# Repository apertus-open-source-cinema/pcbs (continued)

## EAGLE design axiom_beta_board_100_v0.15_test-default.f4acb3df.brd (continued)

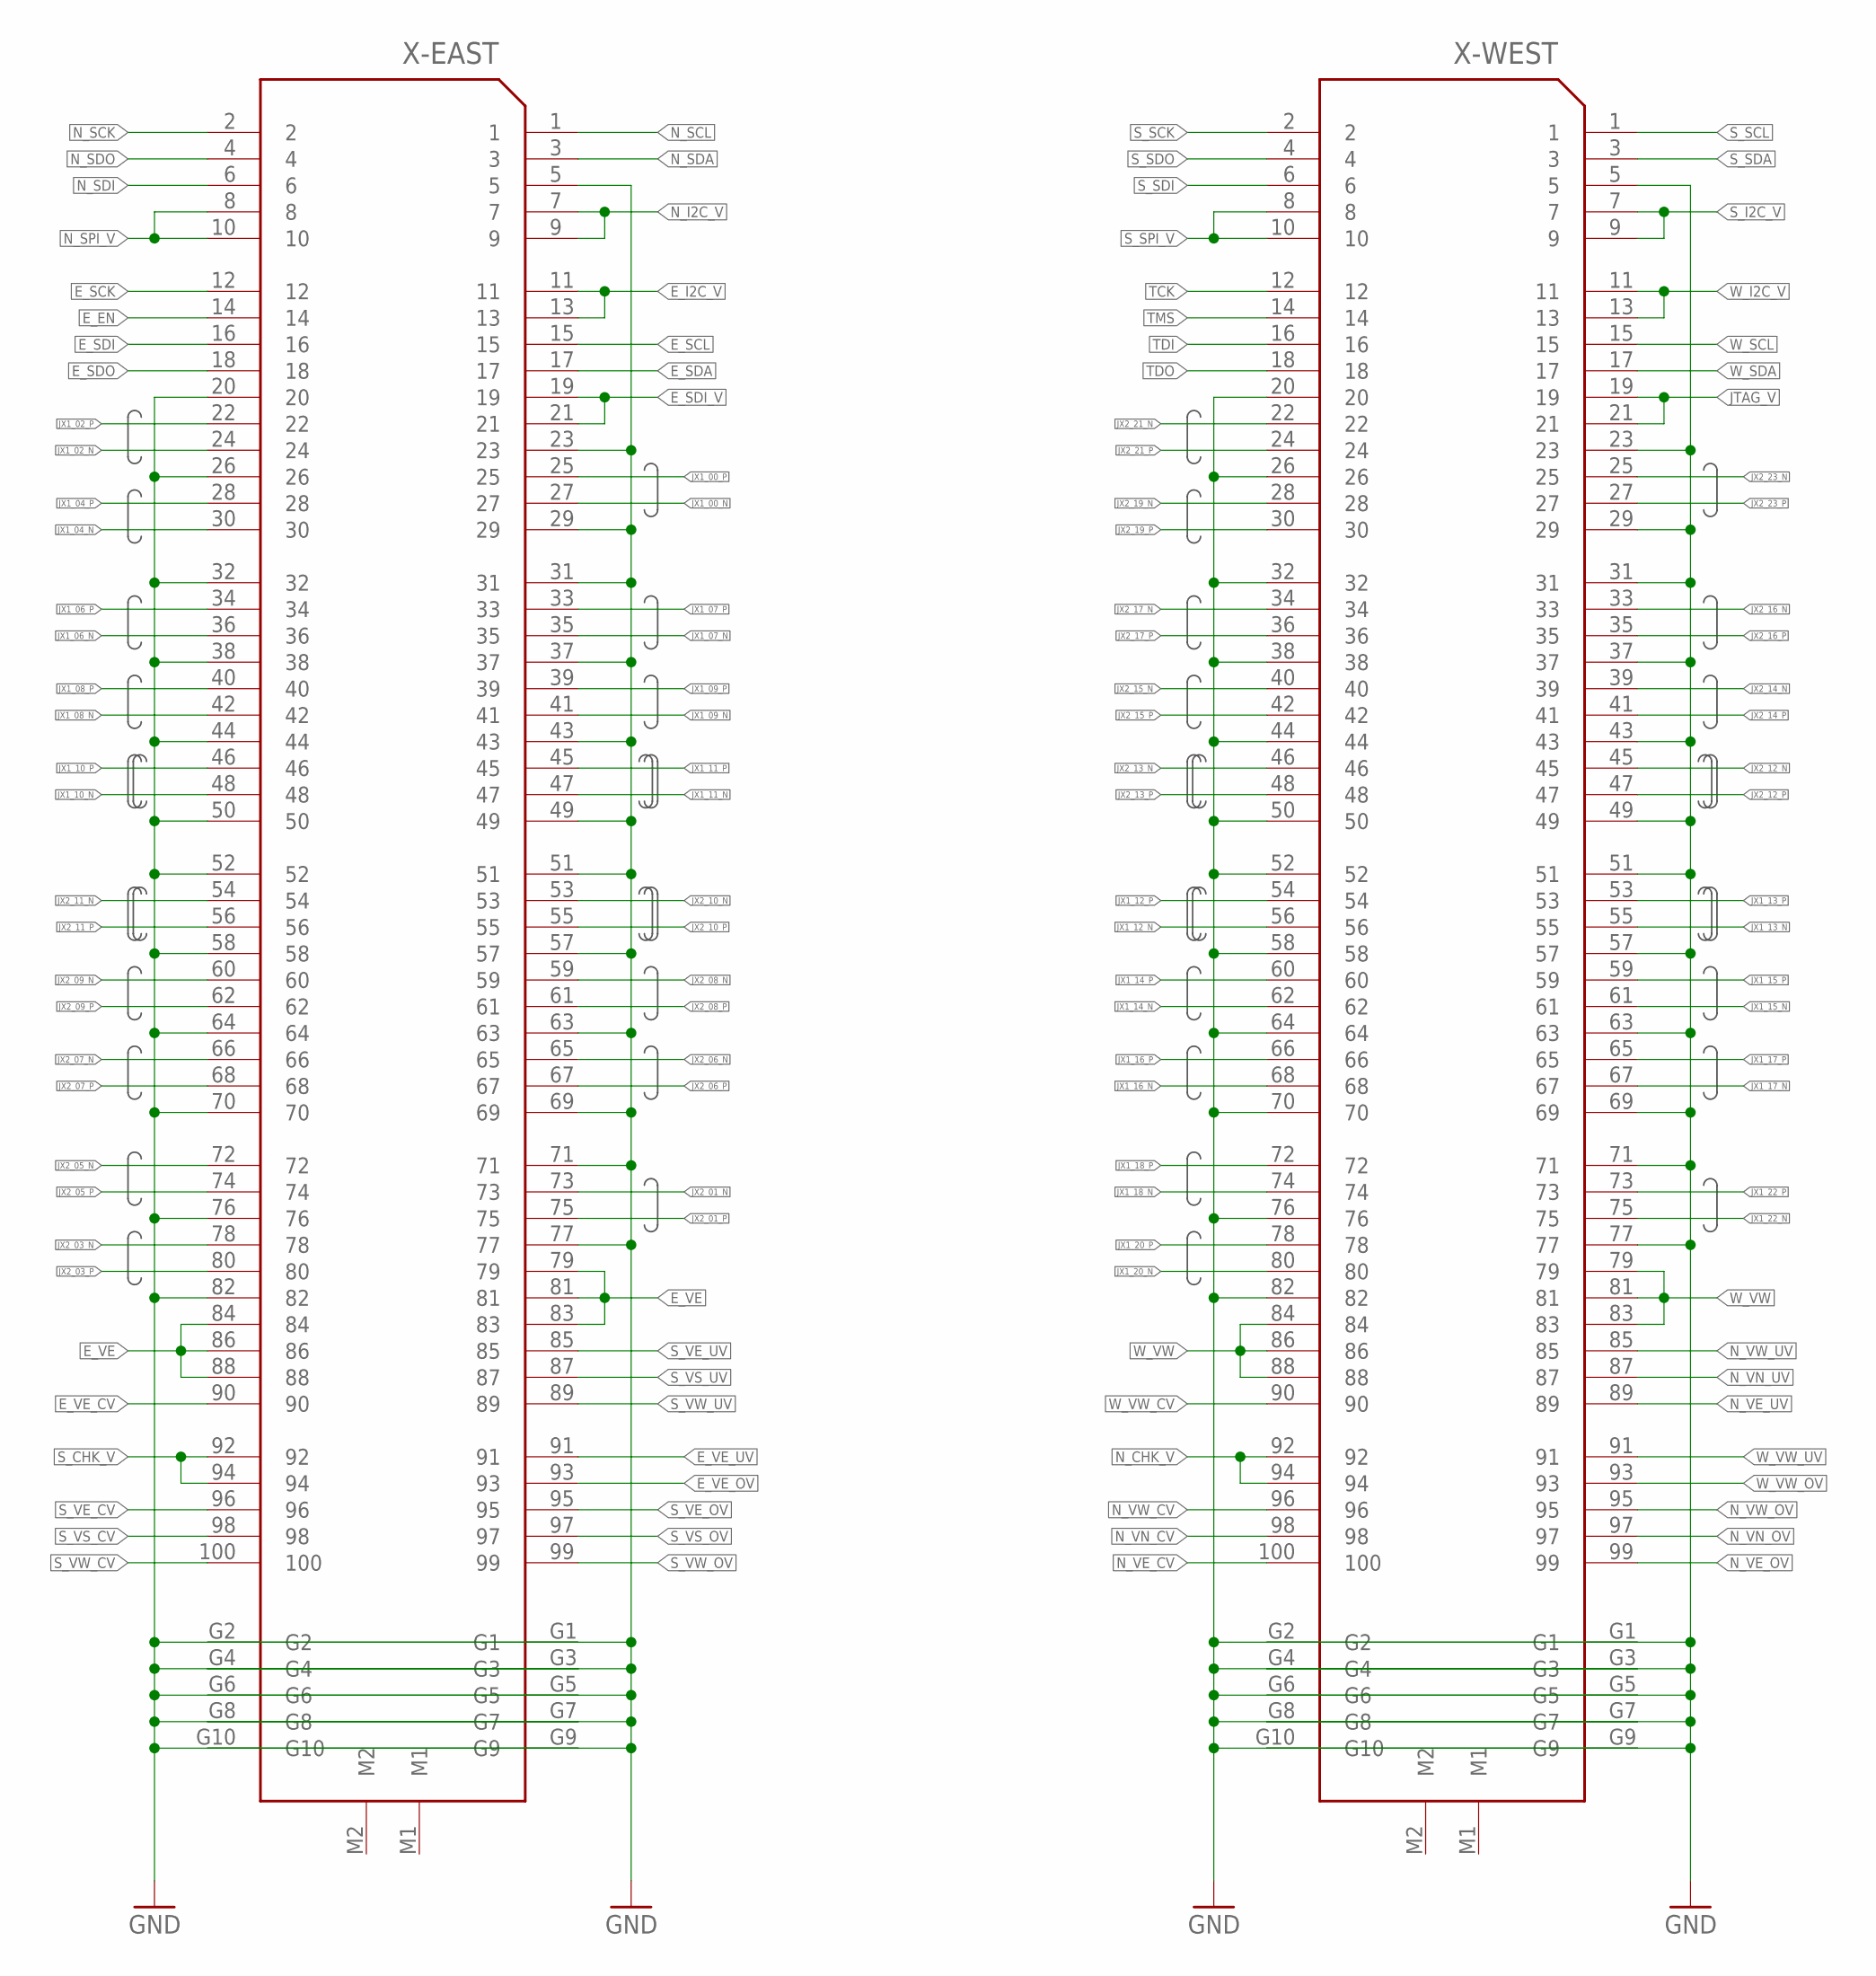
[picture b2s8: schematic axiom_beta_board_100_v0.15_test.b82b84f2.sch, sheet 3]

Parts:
X-EAST: FX10-100/10S; FX10A-100S/10
X-WEST: FX10-100/10S; FX10A-100S/10

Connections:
E_EN: X-EAST.14; also elsewhere on the board
E_I2C_V: X-EAST.11, X-EAST.13; also elsewhere on the board
E_SCK: X-EAST.12; also elsewhere on the board
E_SCL: X-EAST.15; also elsewhere on the board
E_SDA: X-EAST.17; also elsewhere on the board
E_SDI: X-EAST.16; also elsewhere on the board
E_SDI_V: X-EAST.19, X-EAST.21; also elsewhere on the board
E_SDO: X-EAST.18; also elsewhere on the board
E_VE: X-EAST.79, X-EAST.81, X-EAST.83, X-EAST.84, X-EAST.86, X-EAST.88; also elsewhere on the board
E_VE_CV: X-EAST.90; also elsewhere on the board
E_VE_OV: X-EAST.93; also elsewhere on the board
E_VE_UV: X-EAST.91; also elsewhere on the board
GND: X-EAST.5, X-EAST.20, X-EAST.23, X-EAST.26, X-EAST.29, X-EAST.31, X-EAST.32, X-EAST.37, X-EAST.38, X-EAST.43, X-EAST.44, X-EAST.49, X-EAST.50, X-EAST.51, X-EAST.52, X-EAST.57, X-EAST.58, X-EAST.63, X-EAST.64, X-EAST.69, X-EAST.70, X-EAST.71, X-EAST.76, X-EAST.77, X-EAST.82, X-EAST.G1, X-EAST.G2, X-EAST.G3, X-EAST.G4, X-EAST.G5, X-EAST.G6, X-EAST.G7, X-EAST.G8, X-EAST.G9, X-EAST.G10, X-WEST.5, X-WEST.20, X-WEST.23, X-WEST.26, X-WEST.29, X-WEST.31, X-WEST.32, X-WEST.37, X-WEST.38, X-WEST.43, X-WEST.44, X-WEST.49, X-WEST.50, X-WEST.51, X-WEST.52, X-WEST.57, X-WEST.58, X-WEST.63, X-WEST.64, X-WEST.69, X-WEST.70, X-WEST.71, X-WEST.76, X-WEST.77, X-WEST.82, X-WEST.G1, X-WEST.G2, X-WEST.G3, X-WEST.G4, X-WEST.G5, X-WEST.G6, X-WEST.G7, X-WEST.G8, X-WEST.G9, X-WEST.G10; also elsewhere on the board
JTAG_V: X-WEST.19, X-WEST.21; also elsewhere on the board
JX1_00_N: X-EAST.27; also elsewhere on the board
JX1_00_P: X-EAST.25; also elsewhere on the board
JX1_02_N: X-EAST.24; also elsewhere on the board
JX1_02_P: X-EAST.22; also elsewhere on the board
JX1_04_N: X-EAST.30; also elsewhere on the board
JX1_04_P: X-EAST.28; also elsewhere on the board
JX1_06_N: X-EAST.36; also elsewhere on the board
JX1_06_P: X-EAST.34; also elsewhere on the board
JX1_07_N: X-EAST.35; also elsewhere on the board
JX1_07_P: X-EAST.33; also elsewhere on the board
JX1_08_N: X-EAST.42; also elsewhere on the board
JX1_08_P: X-EAST.40; also elsewhere on the board
JX1_09_N: X-EAST.41; also elsewhere on the board
JX1_09_P: X-EAST.39; also elsewhere on the board
JX1_10_N: X-EAST.48; also elsewhere on the board
JX1_10_P: X-EAST.46; also elsewhere on the board
JX1_11_N: X-EAST.47; also elsewhere on the board
JX1_11_P: X-EAST.45; also elsewhere on the board
JX1_12_N: X-WEST.56; also elsewhere on the board
JX1_12_P: X-WEST.54; also elsewhere on the board
JX1_13_N: X-WEST.55; also elsewhere on the board
JX1_13_P: X-WEST.53; also elsewhere on the board
JX1_14_N: X-WEST.62; also elsewhere on the board
JX1_14_P: X-WEST.60; also elsewhere on the board
JX1_15_N: X-WEST.61; also elsewhere on the board
JX1_15_P: X-WEST.59; also elsewhere on the board
JX1_16_N: X-WEST.68; also elsewhere on the board
JX1_16_P: X-WEST.66; also elsewhere on the board
JX1_17_N: X-WEST.67; also elsewhere on the board
JX1_17_P: X-WEST.65; also elsewhere on the board
JX1_18_N: X-WEST.74; also elsewhere on the board
JX1_18_P: X-WEST.72; also elsewhere on the board
JX1_20_N: X-WEST.80; also elsewhere on the board
JX1_20_P: X-WEST.78; also elsewhere on the board
JX1_22_N: X-WEST.75; also elsewhere on the board
JX1_22_P: X-WEST.73; also elsewhere on the board
JX2_01_N: X-EAST.73; also elsewhere on the board
JX2_01_P: X-EAST.75; also elsewhere on the board
JX2_03_N: X-EAST.78; also elsewhere on the board
JX2_03_P: X-EAST.80; also elsewhere on the board
JX2_05_N: X-EAST.72; also elsewhere on the board
JX2_05_P: X-EAST.74; also elsewhere on the board
JX2_06_N: X-EAST.65; also elsewhere on the board
JX2_06_P: X-EAST.67; also elsewhere on the board
JX2_07_N: X-EAST.66; also elsewhere on the board
JX2_07_P: X-EAST.68; also elsewhere on the board
JX2_08_N: X-EAST.59; also elsewhere on the board
JX2_08_P: X-EAST.61; also elsewhere on the board
JX2_09_N: X-EAST.60; also elsewhere on the board
JX2_09_P: X-EAST.62; also elsewhere on the board
JX2_10_N: X-EAST.53; also elsewhere on the board
JX2_10_P: X-EAST.55; also elsewhere on the board
JX2_11_N: X-EAST.54; also elsewhere on the board
JX2_11_P: X-EAST.56; also elsewhere on the board
JX2_12_N: X-WEST.45; also elsewhere on the board
JX2_12_P: X-WEST.47; also elsewhere on the board
JX2_13_N: X-WEST.46; also elsewhere on the board
JX2_13_P: X-WEST.48; also elsewhere on the board
JX2_14_N: X-WEST.39; also elsewhere on the board
JX2_14_P: X-WEST.41; also elsewhere on the board
JX2_15_N: X-WEST.40; also elsewhere on the board
JX2_15_P: X-WEST.42; also elsewhere on the board
JX2_16_N: X-WEST.33; also elsewhere on the board
JX2_16_P: X-WEST.35; also elsewhere on the board
JX2_17_N: X-WEST.34; also elsewhere on the board
JX2_17_P: X-WEST.36; also elsewhere on the board
JX2_19_N: X-WEST.28; also elsewhere on the board
JX2_19_P: X-WEST.30; also elsewhere on the board
JX2_21_N: X-WEST.22; also elsewhere on the board
JX2_21_P: X-WEST.24; also elsewhere on the board
JX2_23_N: X-WEST.25; also elsewhere on the board
JX2_23_P: X-WEST.27; also elsewhere on the board
N_CHK_V: X-WEST.92, X-WEST.94; also elsewhere on the board
N_I2C_V: X-EAST.7, X-EAST.9; also elsewhere on the board
N_SCK: X-EAST.2; also elsewhere on the board
N_SCL: X-EAST.1; also elsewhere on the board
N_SDA: X-EAST.3; also elsewhere on the board
N_SDI: X-EAST.6; also elsewhere on the board
N_SDO: X-EAST.4; also elsewhere on the board
N_SPI_V: X-EAST.8, X-EAST.10; also elsewhere on the board
N_VE_CV: X-WEST.100; also elsewhere on the board
N_VE_OV: X-WEST.99; also elsewhere on the board
N_VE_UV: X-WEST.89; also elsewhere on the board
N_VN_CV: X-WEST.98; also elsewhere on the board
N_VN_OV: X-WEST.97; also elsewhere on the board
N_VN_UV: X-WEST.87; also elsewhere on the board
N_VW_CV: X-WEST.96; also elsewhere on the board
N_VW_OV: X-WEST.95; also elsewhere on the board
N_VW_UV: X-WEST.85; also elsewhere on the board
S_CHK_V: X-EAST.92, X-EAST.94; also elsewhere on the board
S_I2C_V: X-WEST.7, X-WEST.9; also elsewhere on the board
S_SCK: X-WEST.2; also elsewhere on the board
S_SCL: X-WEST.1; also elsewhere on the board
S_SDA: X-WEST.3; also elsewhere on the board
S_SDI: X-WEST.6; also elsewhere on the board
S_SDO: X-WEST.4; also elsewhere on the board
S_SPI_V: X-WEST.8, X-WEST.10; also elsewhere on the board
S_VE_CV: X-EAST.96; also elsewhere on the board
S_VE_OV: X-EAST.95; also elsewhere on the board
S_VE_UV: X-EAST.85; also elsewhere on the board
S_VS_CV: X-EAST.98; also elsewhere on the board
S_VS_OV: X-EAST.97; also elsewhere on the board
S_VS_UV: X-EAST.87; also elsewhere on the board
S_VW_CV: X-EAST.100; also elsewhere on the board
S_VW_OV: X-EAST.99; also elsewhere on the board
S_VW_UV: X-EAST.89; also elsewhere on the board
TCK: X-WEST.12; also elsewhere on the board
TDI: X-WEST.16; also elsewhere on the board
TDO: X-WEST.18; also elsewhere on the board
TMS: X-WEST.14; also elsewhere on the board
W_I2C_V: X-WEST.11, X-WEST.13; also elsewhere on the board
W_SCL: X-WEST.15; also elsewhere on the board
W_SDA: X-WEST.17; also elsewhere on the board
W_VW: X-WEST.79, X-WEST.81, X-WEST.83, X-WEST.84, X-WEST.86, X-WEST.88; also elsewhere on the board
W_VW_CV: X-WEST.90; also elsewhere on the board
W_VW_OV: X-WEST.93; also elsewhere on the board
W_VW_UV: X-WEST.91; also elsewhere on the board

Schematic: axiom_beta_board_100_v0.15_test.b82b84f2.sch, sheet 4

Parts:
C5, C5', C7, C7', C9, C9', C11, C11': C0805-A; 0805-A
C6, C6', C8, C8', C10, C10', C12, C12': C0603-A; 0603-A
HDR-NE: PINHD-2X06_2.00; 2X06M
HDR-NW: PINHD-2X06_2.00; 2X06M
HDR-SE: PINHD-2X06_2.00; 2X06M
HDR-SW: PINHD-2X06_2.00; 2X06M
M-LVDS: PINHD-1X02_2.00; 1X02M
MP-NE: PINHD-1X03_2.00; 1X03M
MP-NW: PINHD-1X02_2.00; 1X02M
MP-SE: PINHD-1X03_2.00; 1X03M
MP-SW: PINHD-1X02_2.00; 1X02M
PB-NW: DF12(XX)-20DP-0.5V
PB-SE: DF12(XX)-20DP-0.5V
PCIE-NORTH: PCIE-36SOCKET; PCIE-36
PCIE-SOUTH: PCIE-36SOCKET; PCIE-36
PWR-NE: PINHD-2X02_2.54; 2X02
PWR-NW: PINHD-2X02_2.54; 2X02
PWR-SE: PINHD-2X02_2.54; 2X02
PWR-SW: PINHD-2X02_2.54; 2X02
SPI-E: PINHD-2X02_2.00; 1X03M
SPI-W: PINHD-2X02_2.00; 1X03M
U$1, U$2, U$11, U$14, U$15, U$16, U$17, U$18, U$19, U$20, U$21, U$22: PINPAD1.27MM; 1.2/0.6

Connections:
BANK13_00_N: PCIE-NORTH.A14 (LVDS_3B); also elsewhere on the board
BANK13_00_P: PCIE-NORTH.A13 (LVDS_3A); also elsewhere on the board
BANK13_01_N: M-LVDS.1; also elsewhere on the board
BANK13_01_P: M-LVDS.2; also elsewhere on the board
BANK13_02_N: PCIE-NORTH.A16 (LVDS_4A); also elsewhere on the board
BANK13_02_P: PCIE-NORTH.A17 (LVDS_4B); also elsewhere on the board
BANK13_03_N: PCIE-NORTH.B16 (LVDS_5A); also elsewhere on the board
BANK13_03_P: PCIE-NORTH.B17 (LVDS_5B); also elsewhere on the board
BANK13_04_N: PCIE-SOUTH.A6 (LVDS_1B); also elsewhere on the board
BANK13_04_P: PCIE-SOUTH.A5 (LVDS_1A); also elsewhere on the board
BANK13_05_N: PCIE-SOUTH.A3 (LVDS_0B); also elsewhere on the board
BANK13_05_P: PCIE-SOUTH.A2 (LVDS_0A); also elsewhere on the board
BANK13_06_N: PCIE-SOUTH.A8 (LVDS_2A); also elsewhere on the board
BANK13_06_P: PCIE-SOUTH.A9 (LVDS_2B); also elsewhere on the board
C_CK_E: SPI-E.2, U$14.1
C_CK_W: SPI-W.2, U$1.1
C_SI_E: SPI-E.1, U$15.1
C_SI_W: SPI-W.1, U$2.1
C_SO_E: SPI-E.3, U$16.1
C_SO_W: SPI-W.3, U$11.1
E_I2C_V: PWR-NE.1; also elsewhere on the board
E_SDI_V: PWR-NE.3; also elsewhere on the board
E_VE: PWR-SE.1; also elsewhere on the board
E_VE_CV: PB-SE.7; also elsewhere on the board
E_VE_OV: PB-SE.10; also elsewhere on the board
E_VE_UV: PB-SE.12; also elsewhere on the board
GND: C5.2, C5'.2, C6.2, C6'.2, C7.2, C7'.2, C8.2, C8'.2, C9.2, C9'.2, C10.2, C10'.2, C11.2, C11'.2, C12.2, C12'.2, MP-NE.1, MP-NE.3, MP-SW.1, MP-SW.2, PB-NW.5, PB-NW.8, PB-NW.9, PB-NW.14, PB-NW.17, PB-SE.5, PB-SE.8, PB-SE.9, PB-SE.14, PB-SE.17, PCIE-NORTH.A1 (GND), PCIE-NORTH.A4 (GND), PCIE-NORTH.A7 (GND), PCIE-NORTH.A10 (GND), PCIE-NORTH.A12 (GND), PCIE-NORTH.A15 (GND), PCIE-NORTH.A18 (GND), PCIE-NORTH.B15 (GND), PCIE-NORTH.B18 (GND), PCIE-SOUTH.A1 (GND), PCIE-SOUTH.A4 (GND), PCIE-SOUTH.A7 (GND), PCIE-SOUTH.A10 (GND), PCIE-SOUTH.A12 (GND), PCIE-SOUTH.A15 (GND), PCIE-SOUTH.A18 (GND), PCIE-SOUTH.B15 (GND), PCIE-SOUTH.B18 (GND), U$17.1, U$20.1; also elsewhere on the board
GPA0_E: HDR-SE.12; also elsewhere on the board
GPA0_W: HDR-NW.12; also elsewhere on the board
GPA1_E: HDR-SE.11; also elsewhere on the board
GPA1_W: HDR-NW.11; also elsewhere on the board
GPA2_E: HDR-SE.10; also elsewhere on the board
GPA2_W: HDR-NW.10; also elsewhere on the board
GPA3_E: HDR-SE.9; also elsewhere on the board
GPA3_W: HDR-NW.9; also elsewhere on the board
GPA4_E: HDR-SE.8; also elsewhere on the board
GPA4_W: HDR-NW.8; also elsewhere on the board
GPA5_E: HDR-SE.7; also elsewhere on the board
GPA5_W: HDR-NW.7; also elsewhere on the board
IOL_2A_N: HDR-NE.1; also elsewhere on the board
IOL_2A_S: HDR-SW.1; also elsewhere on the board
IOL_2B_N: HDR-NE.2; also elsewhere on the board
IOL_2B_S: HDR-SW.2; also elsewhere on the board
IOL_4A_N: HDR-NE.4; also elsewhere on the board
IOL_4A_S: HDR-SW.4; also elsewhere on the board
IOL_4B_N: HDR-NE.3; also elsewhere on the board
IOL_4B_S: HDR-SW.3; also elsewhere on the board
IOL_5A_N: HDR-NE.5; also elsewhere on the board
IOL_5A_S: HDR-SW.5; also elsewhere on the board
IOL_5B_N: HDR-NE.6; also elsewhere on the board
IOL_5B_S: HDR-SW.6; also elsewhere on the board
JTAG_V: PWR-SW.3; also elsewhere on the board
JX1_01_N: HDR-NE.8; also elsewhere on the board
JX1_01_P: HDR-NE.7; also elsewhere on the board
JX1_03_N: HDR-NE.10; also elsewhere on the board
JX1_03_P: HDR-NE.9; also elsewhere on the board
JX1_05_N: HDR-NE.12; also elsewhere on the board
JX1_05_P: HDR-NE.11; also elsewhere on the board
JX1_19_N: PCIE-NORTH.A3 (LVDS_0B); also elsewhere on the board
JX1_19_P: PCIE-NORTH.A2 (LVDS_0A); also elsewhere on the board
JX1_21_N: PCIE-NORTH.A6 (LVDS_1B); also elsewhere on the board
JX1_21_P: PCIE-NORTH.A5 (LVDS_1A); also elsewhere on the board
JX1_23_N: PCIE-NORTH.A9 (LVDS_2B); also elsewhere on the board
JX1_23_P: PCIE-NORTH.A8 (LVDS_2A); also elsewhere on the board
JX2_00_N: HDR-SE.6; also elsewhere on the board
JX2_00_P: HDR-SE.5; also elsewhere on the board
JX2_02_N: HDR-SE.4; also elsewhere on the board
JX2_02_P: HDR-SE.3; also elsewhere on the board
JX2_04_N: HDR-SE.2; also elsewhere on the board
JX2_04_P: HDR-SE.1; also elsewhere on the board
JX2_18_N: PCIE-SOUTH.B17 (LVDS_5B); also elsewhere on the board
JX2_18_P: PCIE-SOUTH.B16 (LVDS_5A); also elsewhere on the board
JX2_20_N: PCIE-SOUTH.A16 (LVDS_4A); also elsewhere on the board
JX2_20_P: PCIE-SOUTH.A17 (LVDS_4B); also elsewhere on the board
JX2_22_N: PCIE-SOUTH.A13 (LVDS_3A); also elsewhere on the board
JX2_22_P: PCIE-SOUTH.A14 (LVDS_3B); also elsewhere on the board
M_V_NW: C5.1, C5'.1, C6.1, C6'.1, PWR-NW.3, U$18.1; also elsewhere on the board
M_V_SE: C7.1, C7'.1, C8.1, C8'.1, PWR-SE.3, U$21.1; also elsewhere on the board
unnamed 266: MP-SE.2; also elsewhere on the board
unnamed: MP-NW.1, PWR-NW.2
unnamed: MP-NW.2, PWR-NW.4
unnamed: HDR-NW.1, PCIE-NORTH.B9 (IO8)
unnamed: HDR-NW.3, PCIE-NORTH.B5 (IO4)
unnamed: HDR-NW.5, PCIE-NORTH.B1 (IO0)
unnamed: HDR-NW.2, PCIE-NORTH.B11 (IO10)
unnamed: HDR-NW.4, PCIE-NORTH.B7 (IO6)
unnamed: HDR-NW.6, PCIE-NORTH.B3 (IO2)
unnamed: MP-SE.3, PWR-SE.2
unnamed: MP-SE.1, PWR-SE.4
unnamed: HDR-SW.8, PCIE-SOUTH.B9 (IO8)
unnamed: HDR-SW.10, PCIE-SOUTH.B1 (IO0)
unnamed: HDR-SW.12, PCIE-SOUTH.B3 (IO2)
unnamed: HDR-SW.11, PCIE-SOUTH.B5 (IO4)
unnamed: HDR-SW.9, PCIE-SOUTH.B7 (IO6)
unnamed: HDR-SW.7, PCIE-SOUTH.B11 (IO10)
N_CHK_V: PB-NW.19; also elsewhere on the board
N_I2C_V: PWR-NE.4; also elsewhere on the board
N_SPI_V: PWR-NE.2; also elsewhere on the board
N_VE_CV: PB-NW.11; also elsewhere on the board
N_VE_OV: PB-NW.2; also elsewhere on the board
N_VE_UV: PB-NW.16; also elsewhere on the board
N_VN_CV: PB-NW.13; also elsewhere on the board
N_VN_OV: PB-NW.4; also elsewhere on the board
N_VN_UV: PB-NW.18; also elsewhere on the board
N_VW_CV: PB-NW.15; also elsewhere on the board
N_VW_OV: PB-NW.6; also elsewhere on the board
N_VW_UV: PB-NW.20; also elsewhere on the board
PCIE_N_V: PCIE-NORTH.B12 (VCC), PCIE-NORTH.B13 (VCC), PCIE-NORTH.B14 (VCC); also elsewhere on the board
PCIE_S_V: PCIE-SOUTH.B12 (VCC), PCIE-SOUTH.B13 (VCC), PCIE-SOUTH.B14 (VCC); also elsewhere on the board
S_CHK_V: PB-SE.19; also elsewhere on the board
S_I2C_V: PWR-SW.4; also elsewhere on the board
S_SPI_V: PWR-SW.2; also elsewhere on the board
S_VE_CV: PB-SE.15; also elsewhere on the board
S_VE_OV: PB-SE.6; also elsewhere on the board
S_VE_UV: PB-SE.20; also elsewhere on the board
S_VS_CV: PB-SE.13; also elsewhere on the board
S_VS_OV: PB-SE.4; also elsewhere on the board
S_VS_UV: PB-SE.18; also elsewhere on the board
S_VW_CV: PB-SE.11; also elsewhere on the board
S_VW_OV: PB-SE.2; also elsewhere on the board
S_VW_UV: PB-SE.16; also elsewhere on the board
VBAT: MP-NE.2; also elsewhere on the board
VIN_HDR_N: C9.1, C9'.1, C10.1, C10'.1, U$19.1; also elsewhere on the board
VIN_HDR_S: C11.1, C11'.1, C12.1, C12'.1, U$22.1; also elsewhere on the board
W_I2C_V: PWR-SW.1; also elsewhere on the board
W_VW: PWR-NW.1; also elsewhere on the board
W_VW_CV: PB-NW.7; also elsewhere on the board
W_VW_OV: PB-NW.10; also elsewhere on the board
W_VW_UV: PB-NW.12; also elsewhere on the board

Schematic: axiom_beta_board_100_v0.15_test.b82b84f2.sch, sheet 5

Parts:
C1, C2, C3, C4: C0402-B; 0402-B
R1, R2, R3, R4: R0402-B; 0402-B
U1, U5: SST25VF020B; SOIC127P600X175-8N
U2, U6: ICE40_LP384-SG32; QFN-32
U3, U7: MCP23018QFN; QFN50P400X400X80-25N
U4, U8: LD6806F; DFN100X150X50-6N

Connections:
!HOLD!_N: U5.7 (!HOLD), U7.7 (GPB7)
!HOLD!_S: U1.7 (!HOLD), U3.7 (GPB7)
!WP!_N: U5.3 (!WP), U7.24 (GPB0)
!WP!_SW: U1.3 (!WP), U3.24 (GPB0)
CDONE_N: U6.11 (CDONE), U7.2 (GPB2)
CDONE_S: U2.11 (CDONE), U3.2 (GPB2)
CRESET_N: U6.10 (CRESET_B), U7.1 (GPB1)
CRESET_S: U2.10 (CRESET_B), U3.1 (GPB1)
E_EN: U6.23 (IOR_39); also elsewhere on the board
E_SCK: U6.29 (IOT_49); also elsewhere on the board
E_SCL: U6.19 (IOR_35); also elsewhere on the board
E_SDA: U6.18 (IOR_34); also elsewhere on the board
E_SDI: U6.22 (IOR_38); also elsewhere on the board
E_SDO: U6.20 (IOR_36); also elsewhere on the board
GND: C1.2, C2.2, C3.2, C4.2, R2.2, R4.2, U1.4 (VSS), U2.3 (GND), U2.21 (GND), U2.EP, U3.23 (VSS), U4.3 (GND), U5.4 (VSS), U6.3 (GND), U6.21 (GND), U6.EP, U7.23 (VSS), U8.3 (GND); also elsewhere on the board
GPA0_E: U7.15 (GPA0); also elsewhere on the board
GPA0_W: U3.15 (GPA0); also elsewhere on the board
GPA1_E: U7.16 (GPA1); also elsewhere on the board
GPA1_W: U3.16 (GPA1); also elsewhere on the board
GPA2_E: U7.17 (GPA2); also elsewhere on the board
GPA2_W: U3.17 (GPA2); also elsewhere on the board
GPA3_E: U7.18 (GPA3); also elsewhere on the board
GPA3_W: U3.18 (GPA3); also elsewhere on the board
GPA4_E: U7.19 (GPA4); also elsewhere on the board
GPA4_W: U3.19 (GPA4); also elsewhere on the board
GPA5_E: U7.20 (GPA5); also elsewhere on the board
GPA5_W: U3.20 (GPA5); also elsewhere on the board
GPA6_E: U7.21 (GPA6)
GPA6_W: U3.21 (GPA6)
GPA7_E: U7.22 (GPA7)
GPA7_W: U3.22 (GPA7)
IOL_2A_N: U6.2 (IOL_2A); also elsewhere on the board
IOL_2A_S: U2.2 (IOL_2A); also elsewhere on the board
IOL_2B_N: U6.1 (IOL_2B); also elsewhere on the board
IOL_2B_S: U2.1 (IOL_2B); also elsewhere on the board
IOL_4A_N: U6.5 (IOL_4A); also elsewhere on the board
IOL_4A_S: U2.5 (IOL_4A); also elsewhere on the board
IOL_4B_N: U6.6 (IOL_4B); also elsewhere on the board
IOL_4B_S: U2.6 (IOL_4B); also elsewhere on the board
IOL_5A_N: U6.8 (IOL_5A); also elsewhere on the board
IOL_5A_S: U2.8 (IOL_5A); also elsewhere on the board
IOL_5B_N: U6.7 (IOL_5B); also elsewhere on the board
IOL_5B_S: U2.7 (IOL_5B); also elsewhere on the board
M_V_NW: C1.1, R1.1, U1.8 (VCC), U2.4 (VCCIO_3), U2.9 (VCCIO_2), U2.16 (VCC_SPI), U2.17 (VCCIO_1), U2.24 (VPP_2V5), U2.28 (VCCIO_0), U3.8 (VDD), U3.12 (!RESET), U4.4 (EN), U4.6 (IN); also elsewhere on the board
M_V_SE: C3.1, R3.1, U5.8 (VCC), U6.4 (VCCIO_3), U6.9 (VCCIO_2), U6.16 (VCC_SPI), U6.17 (VCCIO_1), U6.24 (VPP_2V5), U6.28 (VCCIO_0), U7.8 (VDD), U7.12 (!RESET), U8.4 (EN), U8.6 (IN); also elsewhere on the board
unnamed: R3.2, R4.1, U7.11 (ADDR)
unnamed: R1.2, R2.1, U3.11 (ADDR)
N_SCK: U6.32 (IOT_52); also elsewhere on the board
N_SCL: U6.27 (IOT_47); also elsewhere on the board
N_SDA: U6.26 (IOT_45); also elsewhere on the board
N_SDI: U6.30 (IOT_50); also elsewhere on the board
N_SDO: U6.31 (IOT_53); also elsewhere on the board
SCK_N: U5.6 (SCK), U6.15 (IOB_26_SCK), U7.6 (GPB6)
SCK_S: U1.6 (SCK), U2.15 (IOB_26_SCK), U3.6 (GPB6)
SDI_N: U5.5 (SI), U6.13 (IOB_25_SDI), U7.4 (GPB4)
SDI_S: U1.5 (SI), U2.13 (IOB_25_SDI), U3.4 (GPB4)
SDO_N: U5.2 (SO), U6.12 (IOB_24_SDO), U7.3 (GPB3)
SDO_S: U1.2 (SO), U2.12 (IOB_24_SDO), U3.3 (GPB3)
SS_N: U5.1 (!CE), U6.14 (IOB_27_SS), U7.5 (GPB5)
SS_S: U1.1 (!CE), U2.14 (IOB_27_SS), U3.5 (GPB5)
S_SCK: U2.32 (IOT_52); also elsewhere on the board
S_SCL: U2.27 (IOT_47); also elsewhere on the board
S_SDA: U2.26 (IOT_45); also elsewhere on the board
S_SDI: U2.30 (IOT_50); also elsewhere on the board
S_SDO: U2.31 (IOT_53); also elsewhere on the board
TCK: U2.29 (IOT_49); also elsewhere on the board
TDI: U2.22 (IOR_38); also elsewhere on the board
TDO: U2.20 (IOR_36); also elsewhere on the board
TMS: U2.23 (IOR_39); also elsewhere on the board
V12_NW: C2.1, U2.25 (VCC), U4.1 (OUT)
V12_SE: C4.1, U6.25 (VCC), U8.1 (OUT)
W_SCL: U2.19 (IOR_35); also elsewhere on the board
W_SDA: U2.18 (IOR_34); also elsewhere on the board

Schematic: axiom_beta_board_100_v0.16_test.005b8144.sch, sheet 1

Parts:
ZED1: µZ-FCI-NOHOLES; µZ-NOHOLES

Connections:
GND: ZED1.15 (GND), ZED1.16 (GND), ZED1.21 (GND), ZED1.22 (GND), ZED1.27 (GND), ZED1.28 (GND), ZED1.33 (GND), ZED1.34 (GND), ZED1.39 (GND), ZED1.40 (GND), ZED1.45 (GND), ZED1.46 (GND), ZED1.51 (GND), ZED1.52 (GND), ZED1.65 (GND), ZED1.66 (GND), ZED1.71 (GND), ZED1.72 (GND), ZED1.77 (GND), ZED1.85 (GND), ZED1.86 (GND), ZED1.95 (GND), ZED1.96 (GND), ZED1.115 (GND), ZED1.116 (GND), ZED1.121 (GND), ZED1.122 (GND), ZED1.127 (GND), ZED1.128 (GND), ZED1.133 (GND), ZED1.134 (GND), ZED1.139 (GND), ZED1.140 (GND), ZED1.145 (GND), ZED1.146 (GND), ZED1.151 (GND), ZED1.152 (GND), ZED1.165 (GND), ZED1.166 (GND), ZED1.171 (GND), ZED1.172 (GND), ZED1.177 (GND), ZED1.185 (GND), ZED1.186 (GND), ZED1.191 (GND), ZED1.192 (GND); also elsewhere on the board
unnamed 266: ZED1.112 (VIN_HDR); also elsewhere on the board
PCIE_N_V: ZED1.78 (VCCO_34), ZED1.79 (VCCO_34), ZED1.80 (VCCO_34); also elsewhere on the board
PCIE_S_V: ZED1.178 (VCCO_35), ZED1.179 (VCCO_35), ZED1.180 (VCCO_35); also elsewhere on the board
VBAT: ZED1.7 (FPGA_VBAT); also elsewhere on the board
VCCO_13: ZED1.198 (VCCO_13)
VIN_HDR_N: ZED1.57 (VIN_HDR), ZED1.58 (VIN_HDR), ZED1.59 (VIN_HDR), ZED1.60 (VIN_HDR); also elsewhere on the board
VIN_HDR_S: ZED1.157 (VIN_HDR), ZED1.158 (VIN_HDR), ZED1.159 (VIN_HDR), ZED1.160 (VIN_HDR); also elsewhere on the board

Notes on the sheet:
AXIOM Beta Main Board [Test]
Copyright (C) 2014 H.Poetzl Licensed under CERN OHL v.1.2
FTDI Debug Interface

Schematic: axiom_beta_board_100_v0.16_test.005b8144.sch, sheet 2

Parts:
ZED1: µZ-FCI-NOHOLES; µZ-NOHOLES

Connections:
BANK13_00_N: ZED1.89 (_N); also elsewhere on the board
BANK13_00_P: ZED1.87 (_P); also elsewhere on the board
BANK13_01_N: ZED1.90 (_N); also elsewhere on the board
BANK13_01_P: ZED1.88 (_P); also elsewhere on the board
BANK13_02_N: ZED1.93 (_N); also elsewhere on the board
BANK13_02_P: ZED1.91 (_P); also elsewhere on the board
BANK13_03_N: ZED1.94 (_N); also elsewhere on the board
BANK13_03_P: ZED1.92 (_P); also elsewhere on the board
BANK13_04_N: ZED1.195 (_N); also elsewhere on the board
BANK13_04_P: ZED1.193 (_P); also elsewhere on the board
BANK13_05_N: ZED1.196 (_N); also elsewhere on the board
BANK13_05_P: ZED1.194 (_P); also elsewhere on the board
BANK13_06_N: ZED1.199 (_N); also elsewhere on the board
BANK13_06_P: ZED1.197 (_P); also elsewhere on the board
JX1_00_N: ZED1.13 (_N); also elsewhere on the board
JX1_00_P: ZED1.11 (_P); also elsewhere on the board
JX1_01_N: ZED1.14 (_N); also elsewhere on the board
JX1_01_P: ZED1.12 (_P); also elsewhere on the board
JX1_02_N: ZED1.19 (_N); also elsewhere on the board
JX1_02_P: ZED1.17 (_P); also elsewhere on the board
JX1_03_N: ZED1.20 (_N); also elsewhere on the board
JX1_03_P: ZED1.18 (_P); also elsewhere on the board
JX1_04_N: ZED1.25 (_N); also elsewhere on the board
JX1_04_P: ZED1.23 (_P); also elsewhere on the board
JX1_05_N: ZED1.26 (_N); also elsewhere on the board
JX1_05_P: ZED1.24 (_P); also elsewhere on the board
JX1_06_N: ZED1.31 (_N); also elsewhere on the board
JX1_06_P: ZED1.29 (_P); also elsewhere on the board
JX1_07_N: ZED1.32 (_N); also elsewhere on the board
JX1_07_P: ZED1.30 (_P); also elsewhere on the board
JX1_08_N: ZED1.37 (_N); also elsewhere on the board
JX1_08_P: ZED1.35 (_P); also elsewhere on the board
JX1_09_N: ZED1.38 (_N); also elsewhere on the board
JX1_09_P: ZED1.36 (_P); also elsewhere on the board
JX1_10_N: ZED1.43 (_N); also elsewhere on the board
JX1_10_P: ZED1.41 (_P); also elsewhere on the board
JX1_11_N: ZED1.44 (_N); also elsewhere on the board
JX1_11_P: ZED1.42 (_P); also elsewhere on the board
JX1_12_N: ZED1.49 (_N); also elsewhere on the board
JX1_12_P: ZED1.47 (_P); also elsewhere on the board
JX1_13_N: ZED1.50 (_N); also elsewhere on the board
JX1_13_P: ZED1.48 (_P); also elsewhere on the board
JX1_14_N: ZED1.55 (_N); also elsewhere on the board
JX1_14_P: ZED1.53 (_P); also elsewhere on the board
JX1_15_N: ZED1.56 (_N); also elsewhere on the board
JX1_15_P: ZED1.54 (_P); also elsewhere on the board
JX1_16_N: ZED1.63 (_N); also elsewhere on the board
JX1_16_P: ZED1.61 (_P); also elsewhere on the board
JX1_17_N: ZED1.64 (_N); also elsewhere on the board
JX1_17_P: ZED1.62 (_P); also elsewhere on the board
JX1_18_N: ZED1.69 (_N); also elsewhere on the board
JX1_18_P: ZED1.67 (_P); also elsewhere on the board
JX1_19_N: ZED1.70 (_N); also elsewhere on the board
JX1_19_P: ZED1.68 (_P); also elsewhere on the board
JX1_20_N: ZED1.75 (_N); also elsewhere on the board
JX1_20_P: ZED1.73 (_P); also elsewhere on the board
JX1_21_N: ZED1.76 (_N); also elsewhere on the board
JX1_21_P: ZED1.74 (_P); also elsewhere on the board
JX1_22_N: ZED1.83 (_N); also elsewhere on the board
JX1_22_P: ZED1.81 (_P); also elsewhere on the board
JX1_23_N: ZED1.84 (_N); also elsewhere on the board
JX1_23_P: ZED1.82 (_P); also elsewhere on the board
JX2_00_N: ZED1.119 (_N); also elsewhere on the board
JX2_00_P: ZED1.117 (_P); also elsewhere on the board
JX2_01_N: ZED1.120 (_N); also elsewhere on the board
JX2_01_P: ZED1.118 (_P); also elsewhere on the board
JX2_02_N: ZED1.125 (_N); also elsewhere on the board
JX2_02_P: ZED1.123 (_P); also elsewhere on the board
JX2_03_N: ZED1.126 (_N); also elsewhere on the board
JX2_03_P: ZED1.124 (_P); also elsewhere on the board
JX2_04_N: ZED1.131 (_N); also elsewhere on the board
JX2_04_P: ZED1.129 (_P); also elsewhere on the board
JX2_05_N: ZED1.132 (_N); also elsewhere on the board
JX2_05_P: ZED1.130 (_P); also elsewhere on the board
JX2_06_N: ZED1.137 (_N); also elsewhere on the board
JX2_06_P: ZED1.135 (_P); also elsewhere on the board
JX2_07_N: ZED1.138 (_N); also elsewhere on the board
JX2_07_P: ZED1.136 (_P); also elsewhere on the board
JX2_08_N: ZED1.143 (_N); also elsewhere on the board
JX2_08_P: ZED1.141 (_P); also elsewhere on the board
JX2_09_N: ZED1.144 (_N); also elsewhere on the board
JX2_09_P: ZED1.142 (_P); also elsewhere on the board
JX2_10_N: ZED1.149 (_N); also elsewhere on the board
JX2_10_P: ZED1.147 (_P); also elsewhere on the board
JX2_11_N: ZED1.150 (_N); also elsewhere on the board
JX2_11_P: ZED1.148 (_P); also elsewhere on the board
JX2_12_N: ZED1.155 (_N); also elsewhere on the board
JX2_12_P: ZED1.153 (_P); also elsewhere on the board
JX2_13_N: ZED1.156 (_N); also elsewhere on the board
JX2_13_P: ZED1.154 (_P); also elsewhere on the board
JX2_14_N: ZED1.163 (_N); also elsewhere on the board
JX2_14_P: ZED1.161 (_P); also elsewhere on the board
JX2_15_N: ZED1.164 (_N); also elsewhere on the board
JX2_15_P: ZED1.162 (_P); also elsewhere on the board
JX2_16_N: ZED1.169 (_N); also elsewhere on the board
JX2_16_P: ZED1.167 (_P); also elsewhere on the board
JX2_17_N: ZED1.170 (_N); also elsewhere on the board
JX2_17_P: ZED1.168 (_P); also elsewhere on the board
JX2_18_N: ZED1.175 (_N); also elsewhere on the board
JX2_18_P: ZED1.173 (_P); also elsewhere on the board
JX2_19_N: ZED1.176 (_N); also elsewhere on the board
JX2_19_P: ZED1.174 (_P); also elsewhere on the board
JX2_20_N: ZED1.183 (_N); also elsewhere on the board
JX2_20_P: ZED1.181 (_P); also elsewhere on the board
JX2_21_N: ZED1.184 (_N); also elsewhere on the board
JX2_21_P: ZED1.182 (_P); also elsewhere on the board
JX2_22_N: ZED1.189 (_N); also elsewhere on the board
JX2_22_P: ZED1.187 (_P); also elsewhere on the board
JX2_23_N: ZED1.190 (_N); also elsewhere on the board
JX2_23_P: ZED1.188 (_P); also elsewhere on the board

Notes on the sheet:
AXIOM Beta Main Board [Test]
Copyright (C) 2014-2015 H.Poetzl Licensed under CERN OHL v.1.2
ZYNQ LVDS Interface
